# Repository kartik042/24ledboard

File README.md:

## Welcome to GitHub Pages

You can use the [editor on GitHub](https://github.com/kartik042/24ledboard/edit/master/README.md) to maintain and preview the content for your website in Markdown files.

Whenever you commit to this repository, GitHub Pages will run [Jekyll](https://jekyllrb.com/) to rebuild the pages in your site, from the content in your Markdown files.

### Markdown

Markdown is a lightweight and easy-to-use syntax for styling your writing. It includes conventions for

```markdown
Syntax highlighted code block

# Header 1
## Header 2
### Header 3

- Bulleted
- List

1. Numbered
2. List

**Bold** and _Italic_ and `Code` text

[Link](url) and 
```

For more details see [GitHub Flavored Markdown](https://guides.github.com/features/mastering-markdown/).

### Jekyll Themes

Your Pages site will use the layout and styles from the Jekyll theme you have selected in your [repository settings](https://github.com/kartik042/24ledboard/settings). The name of this theme is saved in the Jekyll `_config.yml` configuration file.

### Support or Contact

Having trouble with Pages? Check out our [documentation](https://help.github.com/categories/github-pages-basics/) or [contact support](https://github.com/contact) and we’ll help you sort it out.

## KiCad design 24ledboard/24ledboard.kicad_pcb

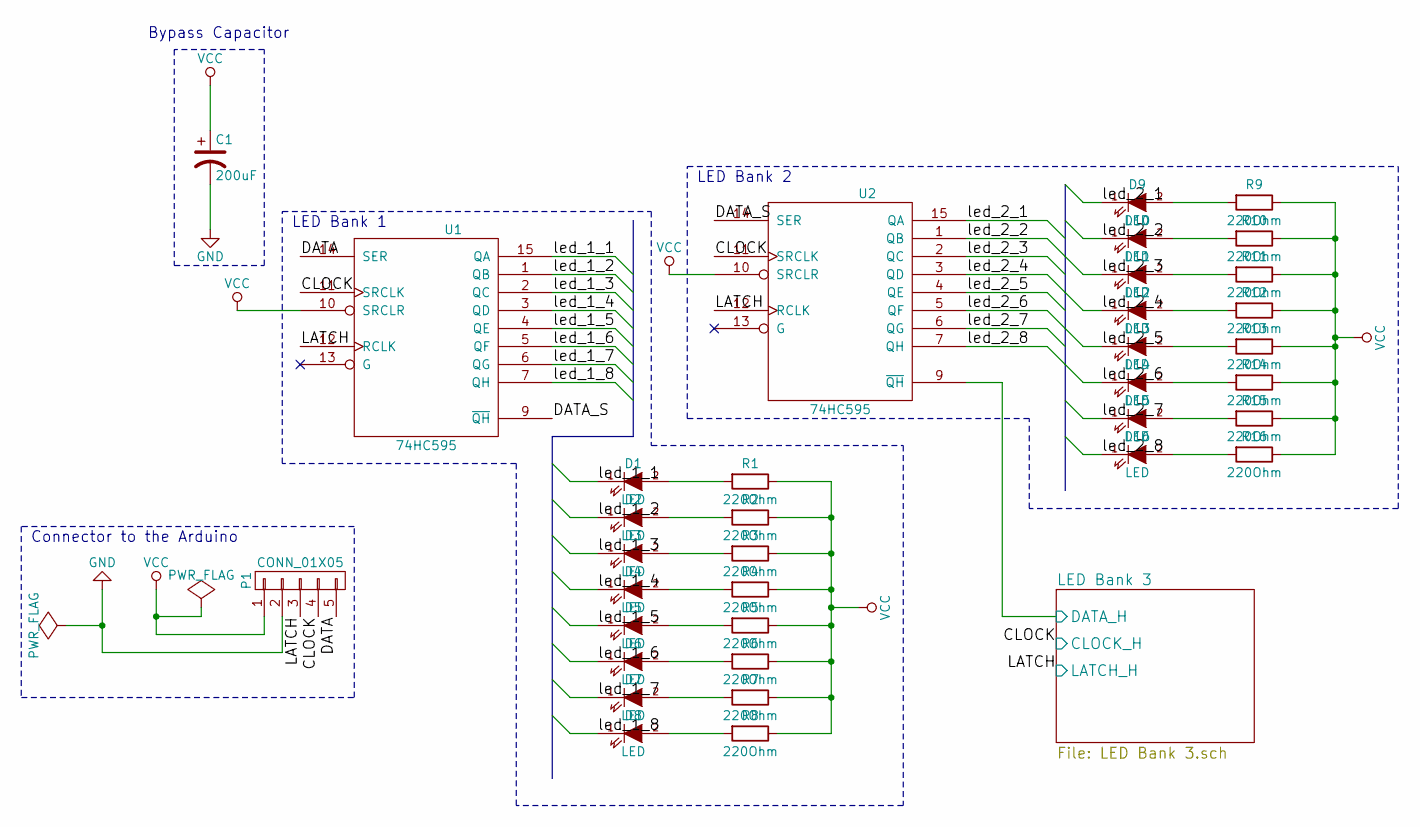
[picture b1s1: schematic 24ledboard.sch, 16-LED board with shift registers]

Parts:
C1: 200uF; c_elec_6.3x5.3
D1, D2, D3, D4, D5, D6, D7, D8, D9, D10, D11, D12, D13, D14, D15, D16: LED; LED_0805
P1: CONN_01X05; Pin_Header_Straight_1x05
R1, R2, R3, R4, R5, R6, R7, R8, R9, R10, R11, R12, R13, R14, R15, R16: 220Ohm; R_0805_HandSoldering
U1, U2: 74HC595; SO-16-N

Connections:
/CLOCK: P1.4, U1.11 (SRCLK), U2.11 (SRCLK); also elsewhere on the board
/DATA: P1.5, U1.14 (SER)
/DATA_S: U1.9 (~QH), U2.14 (SER)
/LATCH: P1.3, U1.12 (RCLK), U2.12 (RCLK); also elsewhere on the board
/LED Bank 3/DATA_H: U2.9 (~QH); also elsewhere on the board
/led_1_1: D1.1 (K), U1.15 (QA)
/led_1_2: D2.1 (K), U1.1 (QB)
/led_1_3: D3.1 (K), U1.2 (QC)
/led_1_4: D4.1 (K), U1.3 (QD)
/led_1_5: D5.1 (K), U1.4 (QE)
/led_1_6: D6.1 (K), U1.5 (QF)
/led_1_7: D7.1 (K), U1.6 (QG)
/led_1_8: D8.1 (K), U1.7 (QH)
/led_2_1: D9.1 (K), U2.15 (QA)
/led_2_2: D10.1 (K), U2.1 (QB)
/led_2_3: D11.1 (K), U2.2 (QC)
/led_2_4: D12.1 (K), U2.3 (QD)
/led_2_5: D13.1 (K), U2.4 (QE)
/led_2_6: D14.1 (K), U2.5 (QF)
/led_2_7: D15.1 (K), U2.6 (QG)
/led_2_8: D16.1 (K), U2.7 (QH)
GND: C1.2, P1.2, U1.8 (GND), U2.8 (GND); also elsewhere on the board
unnamed: D1.2 (A), R1.2
unnamed: D2.2 (A), R2.2
unnamed: D3.2 (A), R3.2
unnamed: D4.2 (A), R4.2
unnamed: D5.2 (A), R5.2
unnamed: D6.2 (A), R6.2
unnamed: D7.2 (A), R7.2
unnamed: D8.2 (A), R8.2
unnamed: D9.2 (A), R9.2
unnamed: D10.2 (A), R10.2
unnamed: D11.2 (A), R11.2
unnamed: D12.2 (A), R12.2
unnamed: D13.2 (A), R13.2
unnamed: D14.2 (A), R14.2
unnamed: D15.2 (A), R15.2
unnamed: D16.2 (A), R16.2
VCC: C1.1, P1.1, R1.1, R2.1, R3.1, R4.1, R5.1, R6.1, R7.1, R8.1, R9.1, R10.1, R11.1, R12.1, R13.1, R14.1, R15.1, R16.1, U1.10 (SRCLR), U1.16 (VCC), U2.10 (SRCLR), U2.16 (VCC); also elsewhere on the board

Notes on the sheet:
Connector to the Arduino
Bypass Capacitor
LED Bank 2
LED Bank 1

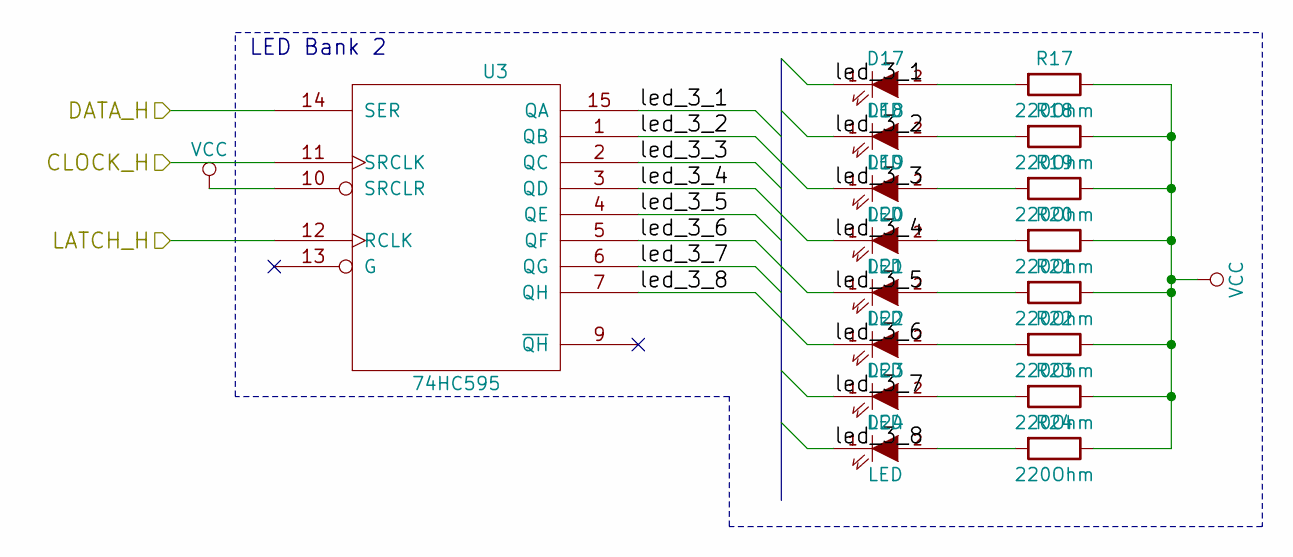
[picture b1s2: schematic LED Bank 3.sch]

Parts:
D17, D18, D19, D20, D21, D22, D23, D24: LED; LED_0805
R17, R18, R19, R20, R21, R22, R23, R24: 220Ohm; R_0805_HandSoldering
U3: 74HC595; SO-16-N

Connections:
/CLOCK: U3.11 (SRCLK); also elsewhere on the board
/LATCH: U3.12 (RCLK); also elsewhere on the board
/LED Bank 3/DATA_H: U3.14 (SER); also elsewhere on the board
/LED Bank 3/led_3_1: D17.1 (K), U3.15 (QA)
/LED Bank 3/led_3_2: D18.1 (K), U3.1 (QB)
/LED Bank 3/led_3_3: D19.1 (K), U3.2 (QC)
/LED Bank 3/led_3_4: D20.1 (K), U3.3 (QD)
/LED Bank 3/led_3_5: D21.1 (K), U3.4 (QE)
/LED Bank 3/led_3_6: D22.1 (K), U3.5 (QF)
/LED Bank 3/led_3_7: D23.1 (K), U3.6 (QG)
/LED Bank 3/led_3_8: D24.1 (K), U3.7 (QH)
GND: U3.8 (GND); also elsewhere on the board
unnamed: D17.2 (A), R17.2
unnamed: D18.2 (A), R18.2
unnamed: D19.2 (A), R19.2
unnamed: D20.2 (A), R20.2
unnamed: D21.2 (A), R21.2
unnamed: D22.2 (A), R22.2
unnamed: D23.2 (A), R23.2
unnamed: D24.2 (A), R24.2
VCC: R17.1, R18.1, R19.1, R20.1, R21.1, R22.1, R23.1, R24.1, U3.10 (SRCLR), U3.16 (VCC); also elsewhere on the board

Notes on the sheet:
LED Bank 2

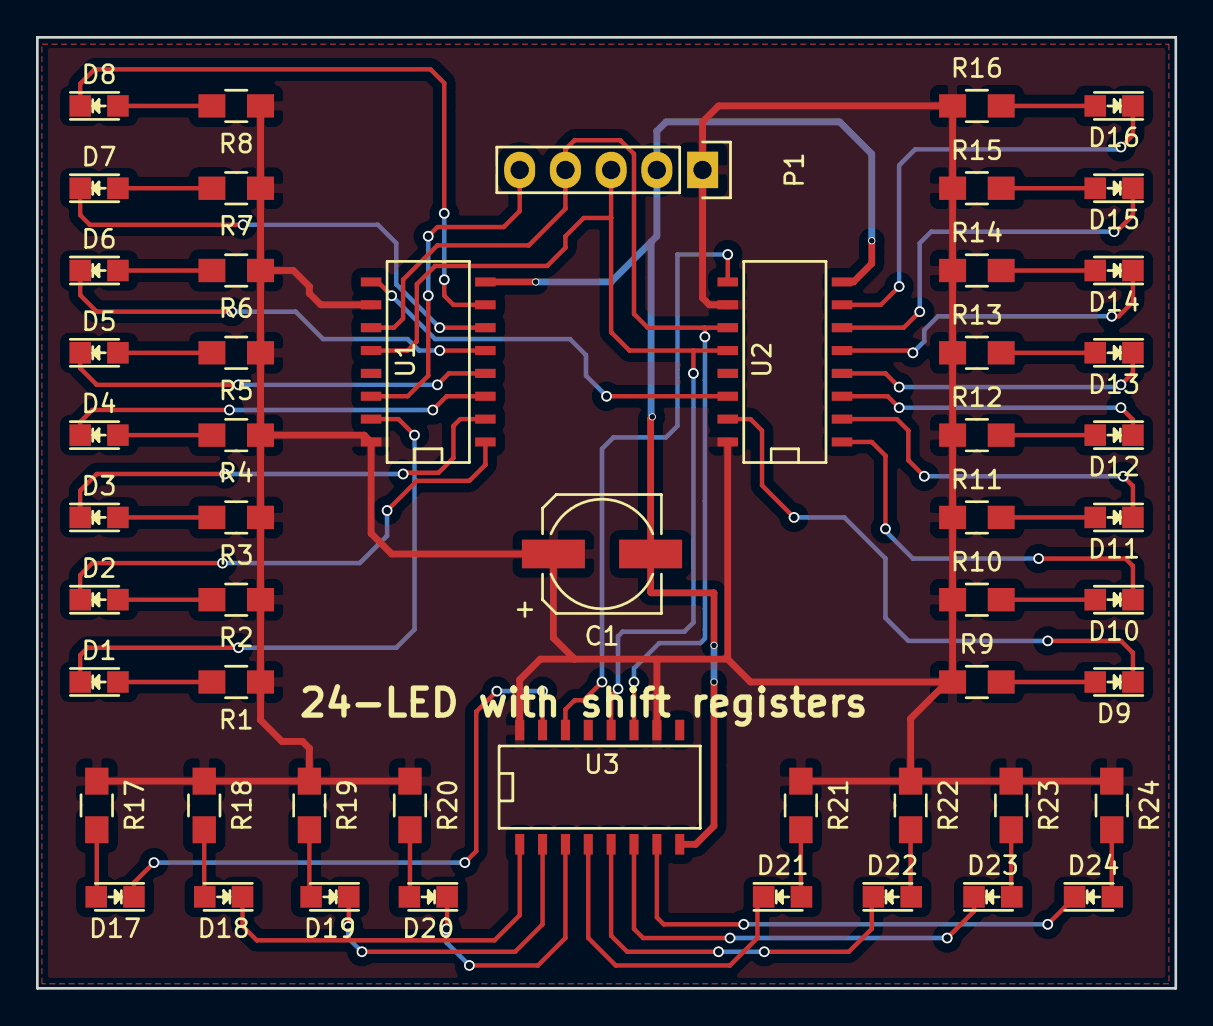
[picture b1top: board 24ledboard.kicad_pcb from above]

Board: 2 copper layers, 63.2 x 52.8 mm, 53 parts (0 on the bottom side), 55 nets.

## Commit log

2017-07-07 Set theme jekyll-theme-slate
